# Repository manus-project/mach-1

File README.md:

# Manus MACH-1

This repository contains designs and assembly instructions for our first generation of manipulator.

 * [Bill of materials](bom.md) - list of materials used
 * [Frame parts](parts) - models of all 3D printer parts
 * [Pritned circuit boards](pcb) - schemes for PCB printing and assembly

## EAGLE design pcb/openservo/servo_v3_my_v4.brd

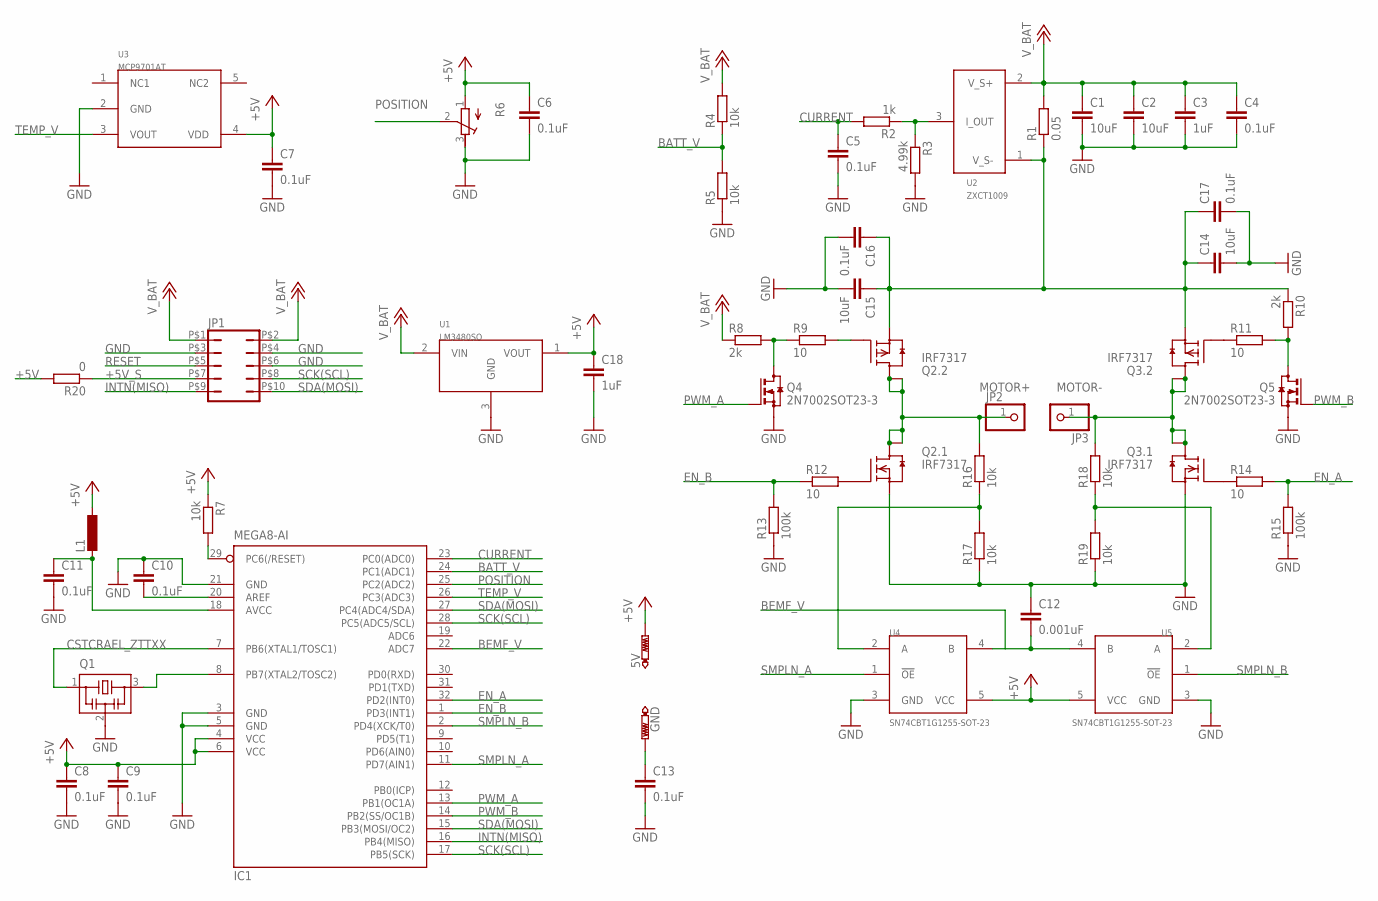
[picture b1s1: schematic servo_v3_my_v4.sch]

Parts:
5V: PTR1B1,27; B1,27
C1, C2, C14, C15: 10uF; C1206
C3, C18: 1uF; C0603
C4, C5, C6, C7, C8, C9, C10, C11, C13, C16, C17: 0.1uF; C0603
C12: 0.001uF; C0603; MPN BFC237052102
GND: PTR1B1,27; B1,27
IC1: MEGA8-AI; TQFP32-08
JP1: JP5QJP5Q_SMD; JP5_DUAL_SIDE
JP2, JP3: PINHD-1X1; 1X01
L1: L-EUL0603; C0603
Q1: CSTCRAEL_ZTTXX; CSTCE_WIDE
Q2, Q3: IRF7317; SO-8
Q4, Q5: 2N7002SOT23-3; SOT23
R1: 0.05; R1206
R2: 1k; R0603
R3: 4.99k; R0603
R4, R5, R7, R16, R17, R18, R19: 10k; R0603
R6: R-TRIMM; RTRIM_SMALL
R8, R10: 2k; R0603
R9, R11, R12, R14: 10; R0603
R13, R15: 100k; R0603
R20: 0; R0603
U1: LM3480SO; SOT23
U2: ZXCT1009; SOT23
U3: MCP9701AT; SC-70-5
U4, U5: SN74CBT1G1255-SOT-23; SOT23-5

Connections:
+5V: 5V.TP, C6.1, C7.1, C8.1, C9.1, C18.1, IC1.4 (VCC), IC1.6 (VCC), L1.1, R6.1 (A), R7.1, R20.2, U1.1 (VOUT), U3.4 (VDD), U4.5 (VCC), U5.5 (VCC)
+5V_S: JP1.P$7 (7), R20.1
BATT_V: IC1.24 (PC1(ADC1)), R4.1, R5.2
BEMF_V: C12.2, IC1.22 (ADC7), U4.4 (B), U5.4 (B)
CURRENT: C5.1, IC1.23 (PC0(ADC0)), R2.2
EN_A: IC1.32 (PD2(INT0)), R14.2, R15.2
EN_B: IC1.1 (PD3(INT1)), R12.1, R13.2
GND: C1.2, C2.2, C3.2, C4.2, C5.2, C6.2, C7.2, C8.2, C9.2, C10.1, C11.2, C12.1, C13.2, C14.2, C15.2, C16.2, C17.2, C18.2, IC1.3 (GND), IC1.5 (GND), IC1.21 (GND), JP1.P$3 (3), JP1.P$4 (4), JP1.P$6 (6), Q1.2, Q2.1 (S), Q3.1 (S), Q4.2 (S), Q5.2 (S), R3.2, R5.1, R6.3 (E), R13.1, R15.1, R17.1, R19.1, U1.3 (GND), U3.2 (GND), U4.3 (GND), U5.3 (GND)
INTN(MISO): IC1.16 (PB4(MISO)), JP1.P$9 (9)
MOTOR+: JP2.1, Q2.5 (D), Q2.6 (D), Q2.7 (D), Q2.8 (D), R16.2
MOTOR-: JP3.1, Q3.5 (D), Q3.6 (D), Q3.7 (D), Q3.8 (D), R18.2
unnamed: R2.1, R3.1, U2.3 (I_OUT)
unnamed: IC1.7 (PB6(XTAL1/TOSC1)), Q1.1
unnamed: IC1.8 (PB7(XTAL2/TOSC2)), Q1.3
unnamed: C11.1, IC1.18 (AVCC), L1.2
unnamed: C10.2, IC1.20 (AREF)
unnamed: C14.1, C15.1, C16.1, C17.1, Q2.3 (S), Q3.3 (S), R1.1, R10.1, U2.1 (V_S-)
unnamed: Q4.3 (D), R8.2, R9.1
unnamed: Q2.4 (G), R9.2
unnamed: Q5.3 (D), R10.2, R11.2
unnamed: C13.1, GND.TP
unnamed: Q2.2 (G), R12.2
unnamed: Q3.2 (G), R14.1
unnamed: Q3.4 (G), R11.1
unnamed: R18.1, R19.2, U5.2 (A)
unnamed: R16.1, R17.2, U4.2 (A)
POSITION: IC1.25 (PC2(ADC2)), R6.2 (S)
PWM_A: IC1.13 (PB1(OC1A)), Q4.1 (G)
PWM_B: IC1.14 (PB2(SS/OC1B)), Q5.1 (G)
RESET: IC1.29 (PC6(/RESET)), JP1.P$5 (5), R7.2
SCK(SCL): IC1.17 (PB5(SCK)), IC1.28 (PC5(ADC5/SCL)), JP1.P$8 (8)
SDA(MOSI): IC1.15 (PB3(MOSI/OC2)), IC1.27 (PC4(ADC4/SDA)), JP1.P$10 (10)
SMPLN_A: IC1.11 (PD7(AIN1)), U4.1 (!OE)
SMPLN_B: IC1.2 (PD4(XCK/T0)), U5.1 (!OE)
TEMP_V: IC1.26 (PC3(ADC3)), U3.3 (VOUT)
V_BAT: C1.1, C2.1, C3.1, C4.1, JP1.P$1 (1), JP1.P$2 (2), R1.2, R4.2, R8.1, U1.2 (VIN), U2.2 (V_S+)

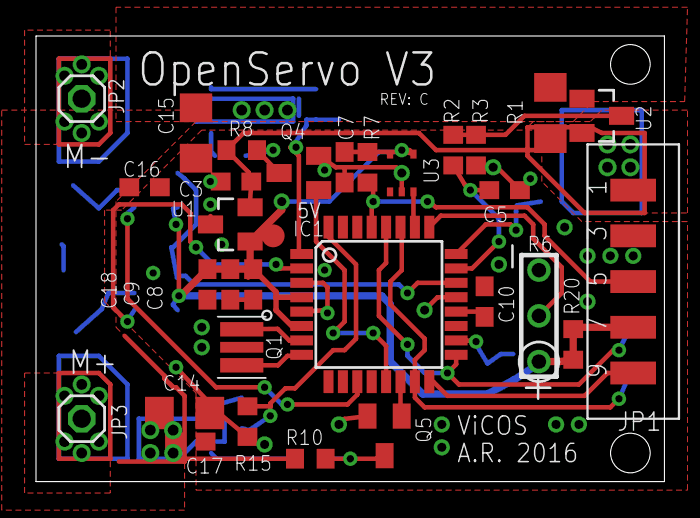
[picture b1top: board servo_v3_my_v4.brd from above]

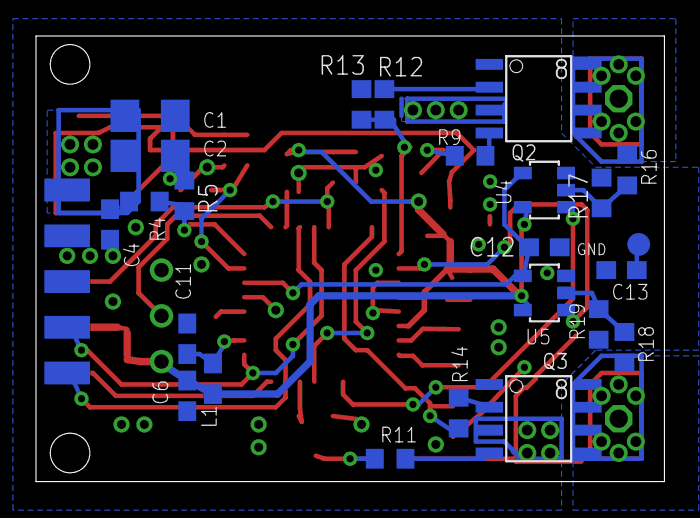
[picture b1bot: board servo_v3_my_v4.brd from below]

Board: 2 copper layers, 34.9 x 24.8 mm, 55 parts (24 on the bottom side), 36 nets.

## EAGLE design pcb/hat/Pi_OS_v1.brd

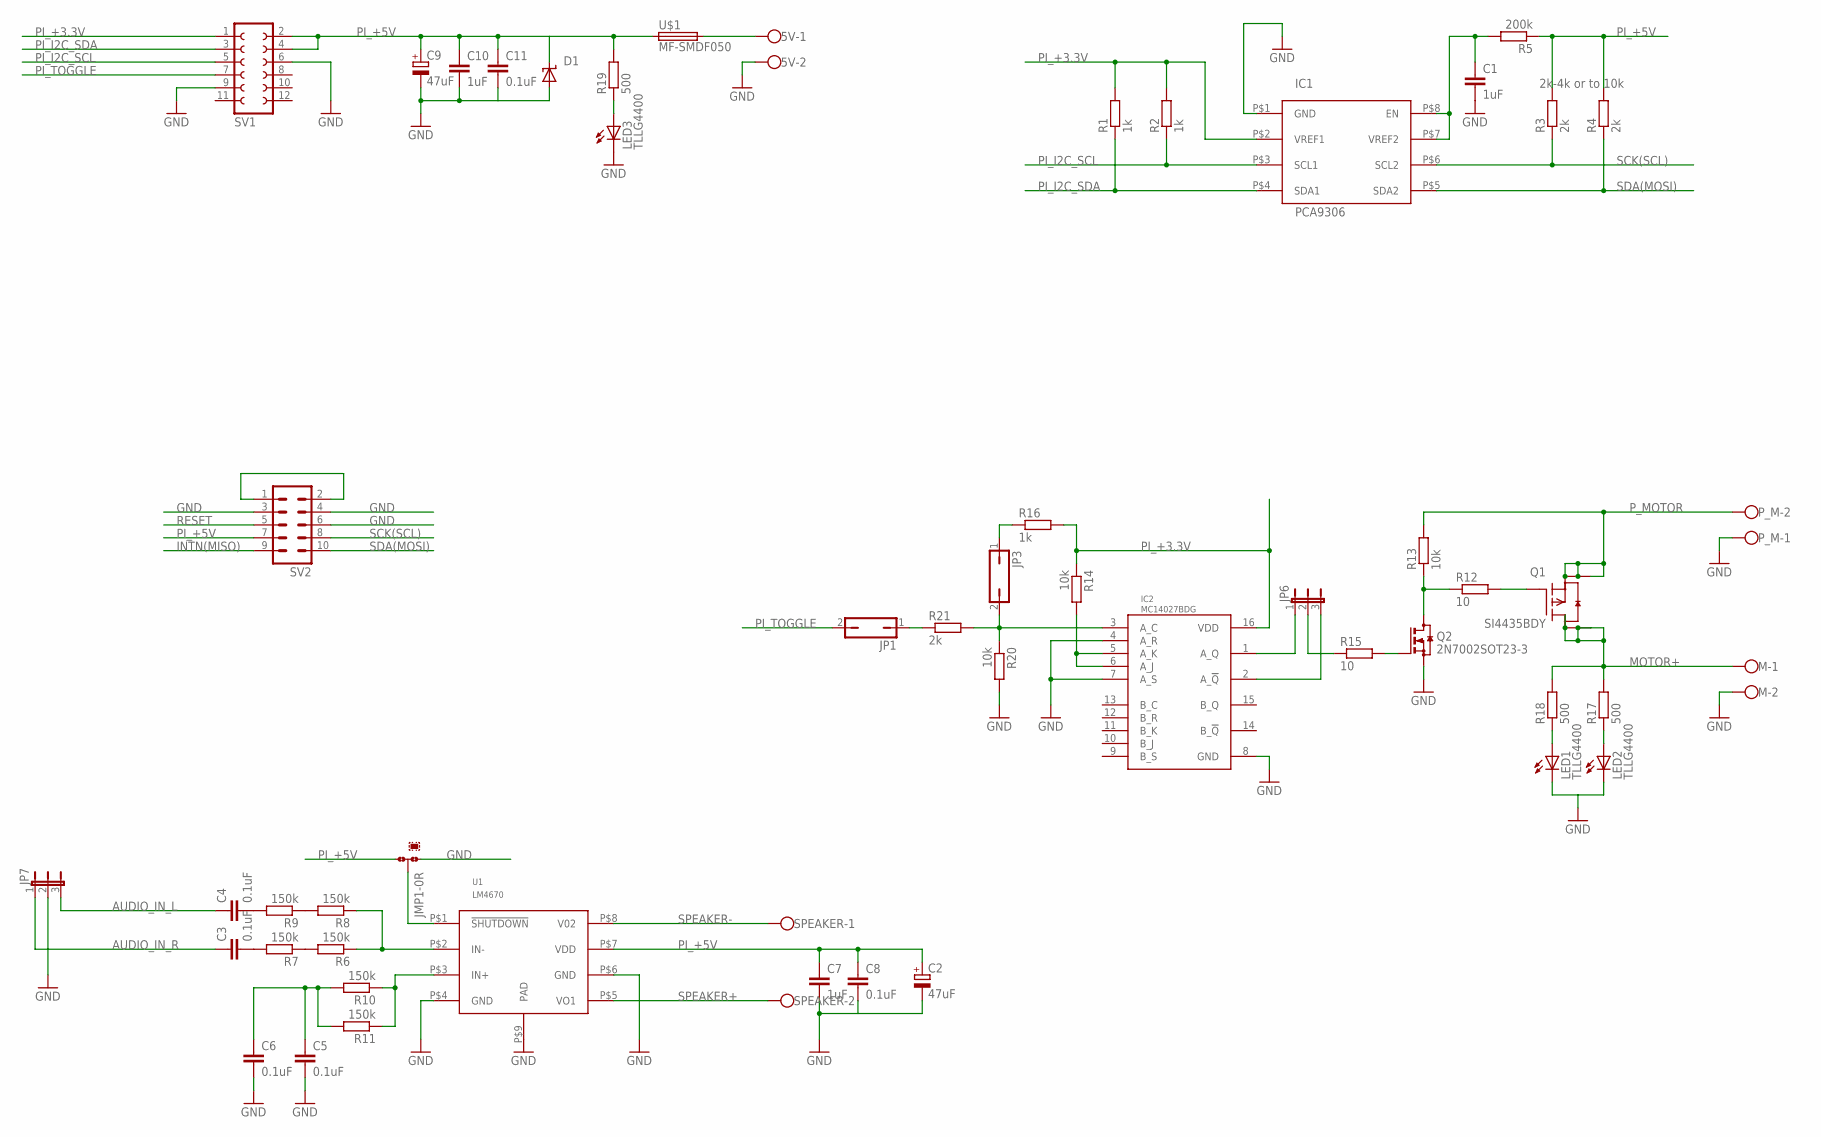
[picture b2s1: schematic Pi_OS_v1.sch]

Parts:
5V: W237-102
C1, C7, C10: 1uF; C1206
C2, C9: 47uF; 153CLV-0505
C3, C4, C5, C6, C8, C11: 0.1uF; C1206
D1: SUPPRESSOR-SMBJ; SMBJ
IC1: PCA9306; TSSOP8
IC2: MC14027BDG; SOIC16
JMP1: 0R-JUMPB; B0R-JMP
JP1, JP3: JP1Q; JP1
JP6, JP7: JP2E; JP2
LED1, LED2, LED3: TLLG4400; LED3MM
M: W237-102
P_M: W237-102
Q1: SI4435BDY; SOIC8
Q2: 2N7002SOT23-3; SOT23
R1, R2, R16: 1k; R0603
R3, R4, R21: 2k; R0603
R5: 200k; R0603
R6, R7, R8, R9, R10, R11: 150k; R0603
R12, R15: 10; R0603
R13, R14, R20: 10k; R0603
R17, R18, R19: 500; R0603
SPEAKER: W237-102
SV1: FE06-2
SV2: MA05-2
U1: LM4670; MSOP-08P
U$1: MF-SMDF050

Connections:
AUDIO_IN_L: C4.1, JP7.3
AUDIO_IN_R: C3.1, JP7.1
GND: 5V.2, C1.2, C2.-, C5.2, C6.2, C7.2, C8.2, C9.-, C10.2, C11.2, D1.A, IC1.P$1 (GND), IC2.4 (A_R), IC2.7 (A_S), IC2.8 (GND), JMP1.1, JP7.2, LED1.K (C), LED2.K (C), LED3.K (C), M.2, P_M.1, Q2.2 (S), R20.2, SV1.6, SV1.9, SV2.3, SV2.4, SV2.6, U1.P$4 (GND), U1.P$6 (GND), U1.P$9 (PAD)
INTN(MISO): SV2.9
MOTOR+: M.1, Q1.5 (D), Q1.6 (D), Q1.7 (D), Q1.8 (D), R17.2, R18.2
unnamed: JP6.2, R15.1
unnamed: IC2.1 (A_Q), JP6.1
unnamed: IC2.2 (A_!Q), JP6.3
unnamed: 5V.1, U$1.2
unnamed: C1.1, IC1.P$7 (VREF2), IC1.P$8 (EN), R5.2
unnamed: IC2.5 (A_K), IC2.6 (A_J), R14.2
unnamed: IC2.3 (A_C), JP3.2, R20.1, R21.2
unnamed: SV2.1, SV2.2
unnamed: R6.1, R8.1, U1.P$2 (IN-)
unnamed: R10.1, R11.1, U1.P$3 (IN+)
unnamed: R6.2, R7.1
unnamed: R8.2, R9.1
unnamed: C3.2, R7.2
unnamed: C4.2, R9.2
unnamed: C5.1, C6.1, R10.2, R11.2
unnamed: Q2.3 (D), R12.1, R13.1
unnamed: Q1.4 (G), R12.2
unnamed: Q2.1 (G), R15.2
unnamed: JP3.1, R16.1
unnamed: JP1.1, R21.1
unnamed: JMP1.2, U1.P$1 (!SHUTDOWN)
unnamed: LED2.A, R17.1
unnamed: LED1.A, R18.1
unnamed: LED3.A, R19.1
PI_+3.3V: IC1.P$2 (VREF1), IC2.16 (VDD), R1.2, R2.2, R14.1, R16.2, SV1.1
PI_+5V: C2.+, C7.1, C8.1, C9.+, C10.1, C11.1, D1.C, JMP1.3, R3.2, R4.2, R5.1, R19.2, SV1.2, SV1.4, SV2.7, U1.P$7 (VDD), U$1.1
PI_I2C_SCL: IC1.P$3 (SCL1), R2.1, SV1.5
PI_I2C_SDA: IC1.P$4 (SDA1), R1.1, SV1.3
PI_TOGGLE: JP1.2, SV1.7
P_MOTOR: P_M.2, Q1.1 (S), Q1.2 (S), Q1.3 (S), R13.2
RESET: SV2.5
SCK(SCL): IC1.P$6 (SCL2), R3.1, SV2.8
SDA(MOSI): IC1.P$5 (SDA2), R4.1, SV2.10
SPEAKER+: SPEAKER.2, U1.P$5 (VO1)
SPEAKER-: SPEAKER.1, U1.P$8 (V02)

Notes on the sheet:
2k-4k or to 10k

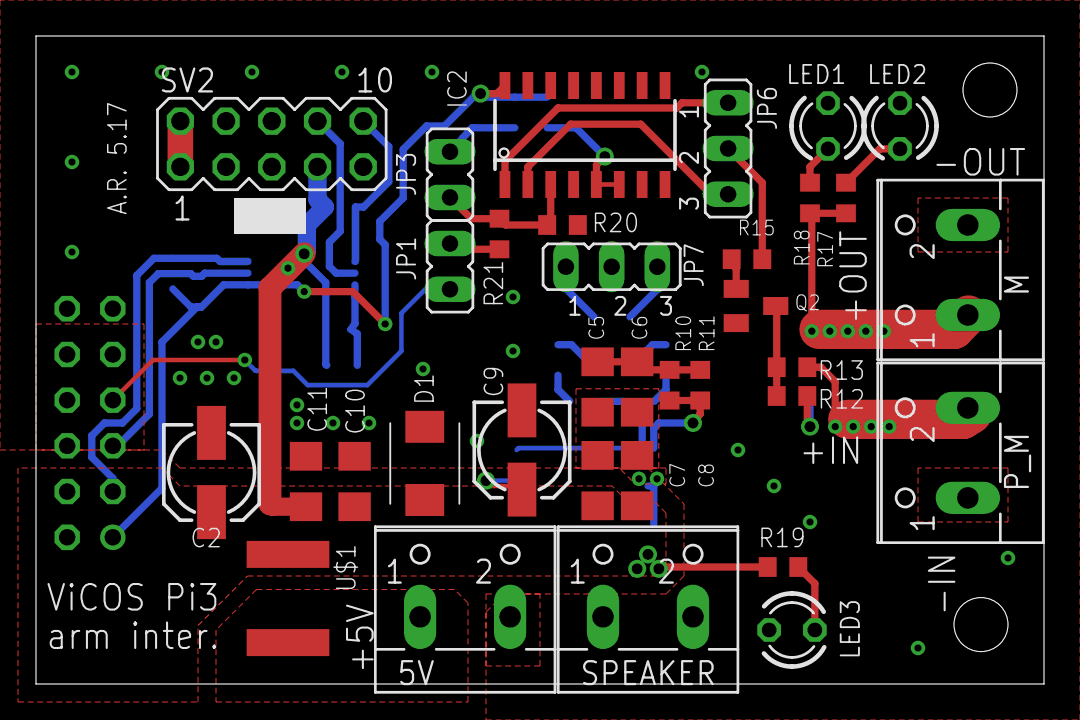
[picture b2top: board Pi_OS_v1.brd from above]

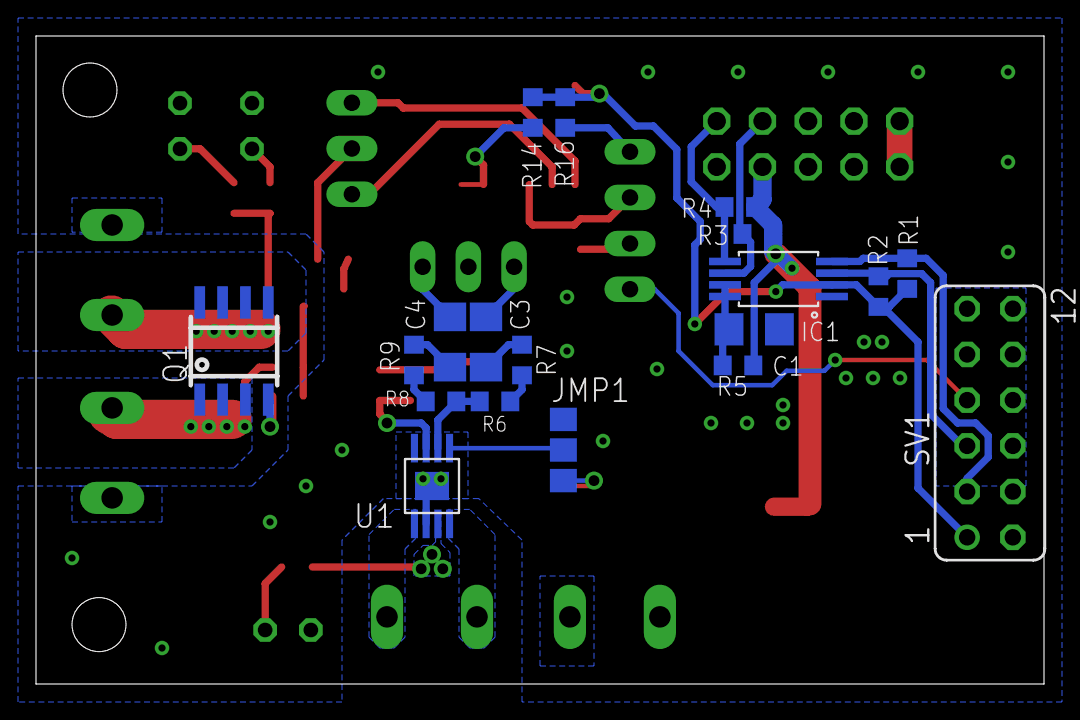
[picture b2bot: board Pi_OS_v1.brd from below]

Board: 2 copper layers, 56.0 x 36.0 mm, 53 parts (19 on the bottom side), 38 nets.

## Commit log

2020-06-01 Initial commit.
2022-10-26 Updating BOM
2022-10-26 Adding PCB files

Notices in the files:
parts and their libraries:
m-pad-2.1: License : GNU General Public License version 2 (see bottom)
SparkFun-Aesthetics: Licensing: Creative Commons ShareAlike 4.0 International - https://creativecommons.org/licenses/by-sa/4.0
